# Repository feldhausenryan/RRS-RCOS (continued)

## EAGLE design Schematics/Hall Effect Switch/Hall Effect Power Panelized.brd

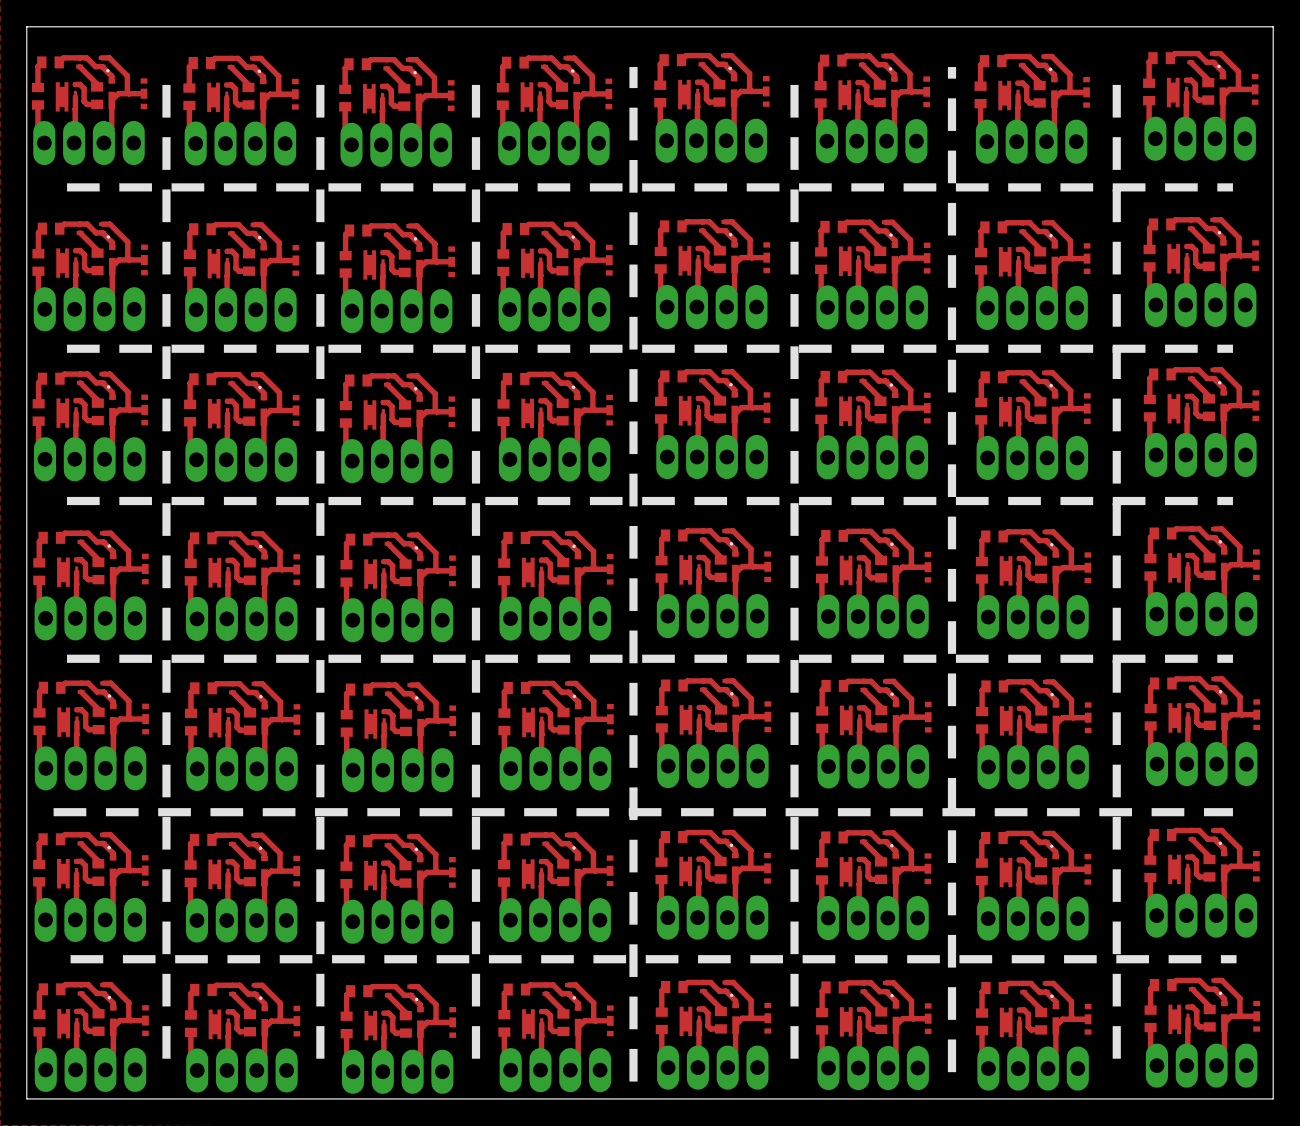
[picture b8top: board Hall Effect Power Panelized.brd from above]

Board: 2 copper layers, 93.0 x 80.0 mm, 560 parts (0 on the bottom side), 337 nets.

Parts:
3.1, 3.2, 3.3, 3.4, 3.5, 3.6, 3.7, 3.8, 3.9, 3.10, 3.11, 3.12, 3.13, 3.14, 3.15, 3.16, 3.17, 3.18, 3.19, 3.20, 3.21, 3.22, 3.23, 3.24, 3.25, 3.26, 3.27, 3.28, 3.29, 3.30, 3.31, 3.32, 3.33, 3.34, 3.35, 3.36, 3.37, 3.38, 3.39, 3.40, 3.41, 3.42, 3.43, 3.44, 3.45, 3.46, 3.47, 3.48, 3.49, 3.50, 3.51, 3.52, 3.53, 3.54, 3.55, 3.56, 3.57, 3.58, 3.59, 3.60, 3.61, 3.62, 3.63, 3.64, 3.65, 3.66, 3.67, 3.68, 3.69, 3.70, 3.71, 3.72, 3.73, 3.74, 3.75, 3.76, 3.77, 3.78, 3.79, 3.80, 3.81, 3.82, 3.83, 3.84, 3.85, 3.86, 3.87, 3.88, 3.89, 3.90, 3.91, 3.92, 3.93, 3.94, 3.95, 3.96, 3.97, 3.98, 3.99, 3.100, 3.101, 3.102, 3.103, 3.104, 3.105, 3.106, 3.107, 3.108, 3.109, 3.110, 3.111, 3.112: RESISTORC0402; C0402
4.7UF, 4.7UF1, 4.7UF2, 4.7UF3, 4.7UF4, 4.7UF5, 4.7UF6, 4.7UF7, 4.7UF8, 4.7UF9, 4.7UF10, 4.7UF11, 4.7UF12, 4.7UF13, 4.7UF14, 4.7UF15, 4.7UF16, 4.7UF17, 4.7UF18, 4.7UF19, 4.7UF20, 4.7UF21, 4.7UF22, 4.7UF23, 4.7UF24, 4.7UF25, 4.7UF26, 4.7UF27, 4.7UF28, 4.7UF29, 4.7UF30, 4.7UF31, 4.7UF32, 4.7UF33, 4.7UF34, 4.7UF35, 4.7UF36, 4.7UF37, 4.7UF38, 4.7UF39, 4.7UF40, 4.7UF41, 4.7UF42, 4.7UF43, 4.7UF44, 4.7UF45, 4.7UF46, 4.7UF47, 4.7UF48, 4.7UF49, 4.7UF50, 4.7UF51, 4.7UF52, 4.7UF53, 4.7UF54, 4.7UF55: CAPACITORC0402; C0402
U$1, U$8, U$15, U$22, U$29, U$36, U$43, U$50, U$57, U$64, U$71, U$78, U$85, U$92, U$99, U$106, U$113, U$120, U$127, U$134, U$141, U$148, U$155, U$162, U$169, U$176, U$183, U$190, U$197, U$204, U$211, U$218, U$225, U$232, U$239, U$246, U$253, U$260, U$267, U$274, U$281, U$288, U$295, U$302, U$309, U$316, U$323, U$330, U$337, U$344, U$351, U$358, U$365, U$372, U$379, U$386: HALL-MOSFET-NEW
U$2, U$9, U$16, U$23, U$30, U$37, U$44, U$51, U$58, U$65, U$72, U$79, U$86, U$93, U$100, U$107, U$114, U$121, U$128, U$135, U$142, U$149, U$156, U$163, U$170, U$177, U$184, U$191, U$198, U$205, U$212, U$219, U$226, U$233, U$240, U$247, U$254, U$261, U$268, U$275, U$282, U$289, U$296, U$303, U$310, U$317, U$324, U$331, U$338, U$345, U$352, U$359, U$366, U$373, U$380, U$387: HALL-HALL-NEW
U$3, U$10, U$17, U$24, U$31, U$38, U$45, U$52, U$59, U$66, U$73, U$80, U$87, U$94, U$101, U$108, U$115, U$122, U$129, U$136, U$143, U$150, U$157, U$164, U$171, U$178, U$185, U$192, U$199, U$206, U$213, U$220, U$227, U$234, U$241, U$248, U$255, U$262, U$269, U$276, U$283, U$290, U$297, U$304, U$311, U$318, U$325, U$332, U$339, U$346, U$353, U$360, U$367, U$374, U$381, U$388: HALL-REG-NEW
U$4, U$5, U$6, U$7, U$11, U$12, U$13, U$14, U$18, U$19, U$20, U$21, U$25, U$26, U$27, U$28, U$32, U$33, U$34, U$35, U$39, U$40, U$41, U$42, U$46, U$47, U$48, U$49, U$53, U$54, U$55, U$56, U$60, U$61, U$62, U$63, U$67, U$68, U$69, U$70, U$74, U$75, U$76, U$77, U$81, U$82, U$83, U$84, U$88, U$89, U$90, U$91, U$95, U$96, U$97, U$98, U$102, U$103, U$104, U$105, U$109, U$110, U$111, U$112, U$116, U$117, U$118, U$119, U$123, U$124, U$125, U$126, U$130, U$131, U$132, U$133, U$137, U$138, U$139, U$140, U$144, U$145, U$146, U$147, U$151, U$152, U$153, U$154, U$158, U$159, U$160, U$161, U$165, U$166, U$167, U$168, U$172, U$173, U$174, U$175, U$179, U$180, U$181, U$182, U$186, U$187, U$188, U$189, U$193, U$194, U$195, U$196, U$200, U$201, U$202, U$203, U$207, U$208, U$209, U$210, U$214, U$215, U$216, U$217, U$221, U$222, U$223, U$224, U$228, U$229, U$230, U$231, U$235, U$236, U$237, U$238, U$242, U$243, U$244, U$245, U$249, U$250, U$251, U$252, U$256, U$257, U$258, U$259, U$263, U$264, U$265, U$266, U$270, U$271, U$272, U$273, U$277, U$278, U$279, U$280, U$284, U$285, U$286, U$287, U$291, U$292, U$293, U$294, U$298, U$299, U$300, U$301, U$305, U$306, U$307, U$308, U$312, U$313, U$314, U$315, U$319, U$320, U$321, U$322, U$326, U$327, U$328, U$329, U$333, U$334, U$335, U$336, U$340, U$341, U$342, U$343, U$347, U$348, U$349, U$350, U$354, U$355, U$356, U$357, U$361, U$362, U$363, U$364, U$368, U$369, U$370, U$371, U$375, U$376, U$377, U$378, U$382, U$383, U$384, U$385, U$389, U$390, U$391, U$392: SINGLE-WIRE

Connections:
GND: 3.3.1, U$2.GND, U$3.2, U$3.5, U$4.P$1, U$7.P$1
GND1: 3.2.1, U$9.GND, U$10.2, U$10.5, U$11.P$1, U$14.P$1
GND2: 3.5.1, U$16.GND, U$17.2, U$17.5, U$18.P$1, U$21.P$1
GND3: 3.7.1, U$23.GND, U$24.2, U$24.5, U$25.P$1, U$28.P$1
GND4: 3.9.1, U$30.GND, U$31.2, U$31.5, U$32.P$1, U$35.P$1
GND5: 3.11.1, U$37.GND, U$38.2, U$38.5, U$39.P$1, U$42.P$1
GND6: 3.13.1, U$44.GND, U$45.2, U$45.5, U$46.P$1, U$49.P$1
GND7: 3.15.1, U$51.GND, U$52.2, U$52.5, U$53.P$1, U$56.P$1
GND8: 3.17.1, U$58.GND, U$59.2, U$59.5, U$60.P$1, U$63.P$1
GND9: 3.19.1, U$65.GND, U$66.2, U$66.5, U$67.P$1, U$70.P$1
GND10: 3.21.1, U$72.GND, U$73.2, U$73.5, U$74.P$1, U$77.P$1
GND11: 3.23.1, U$79.GND, U$80.2, U$80.5, U$81.P$1, U$84.P$1
GND12: 3.25.1, U$86.GND, U$87.2, U$87.5, U$88.P$1, U$91.P$1
GND13: 3.27.1, U$93.GND, U$94.2, U$94.5, U$95.P$1, U$98.P$1
GND14: 3.29.1, U$100.GND, U$101.2, U$101.5, U$102.P$1, U$105.P$1
GND15: 3.31.1, U$107.GND, U$108.2, U$108.5, U$109.P$1, U$112.P$1
GND16: 3.33.1, U$114.GND, U$115.2, U$115.5, U$116.P$1, U$119.P$1
GND17: 3.35.1, U$121.GND, U$122.2, U$122.5, U$123.P$1, U$126.P$1
GND18: 3.37.1, U$128.GND, U$129.2, U$129.5, U$130.P$1, U$133.P$1
GND19: 3.39.1, U$135.GND, U$136.2, U$136.5, U$137.P$1, U$140.P$1
GND20: 3.41.1, U$142.GND, U$143.2, U$143.5, U$144.P$1, U$147.P$1
GND21: 3.43.1, U$149.GND, U$150.2, U$150.5, U$151.P$1, U$154.P$1
GND22: 3.45.1, U$156.GND, U$157.2, U$157.5, U$158.P$1, U$161.P$1
GND23: 3.47.1, U$163.GND, U$164.2, U$164.5, U$165.P$1, U$168.P$1
GND24: 3.49.1, U$170.GND, U$171.2, U$171.5, U$172.P$1, U$175.P$1
GND25: 3.51.1, U$177.GND, U$178.2, U$178.5, U$179.P$1, U$182.P$1
GND26: 3.53.1, U$184.GND, U$185.2, U$185.5, U$186.P$1, U$189.P$1
GND27: 3.55.1, U$191.GND, U$192.2, U$192.5, U$193.P$1, U$196.P$1
GND28: 3.57.1, U$198.GND, U$199.2, U$199.5, U$200.P$1, U$203.P$1
GND29: 3.59.1, U$205.GND, U$206.2, U$206.5, U$207.P$1, U$210.P$1
GND30: 3.61.1, U$212.GND, U$213.2, U$213.5, U$214.P$1, U$217.P$1
GND31: 3.63.1, U$219.GND, U$220.2, U$220.5, U$221.P$1, U$224.P$1
GND32: 3.65.1, U$226.GND, U$227.2, U$227.5, U$228.P$1, U$231.P$1
GND33: 3.67.1, U$233.GND, U$234.2, U$234.5, U$235.P$1, U$238.P$1
GND34: 3.69.1, U$240.GND, U$241.2, U$241.5, U$242.P$1, U$245.P$1
GND35: 3.71.1, U$247.GND, U$248.2, U$248.5, U$249.P$1, U$252.P$1
GND36: 3.73.1, U$254.GND, U$255.2, U$255.5, U$256.P$1, U$259.P$1
GND37: 3.75.1, U$261.GND, U$262.2, U$262.5, U$263.P$1, U$266.P$1
GND38: 3.77.1, U$268.GND, U$269.2, U$269.5, U$270.P$1, U$273.P$1
GND39: 3.79.1, U$275.GND, U$276.2, U$276.5, U$277.P$1, U$280.P$1
GND40: 3.81.1, U$282.GND, U$283.2, U$283.5, U$284.P$1, U$287.P$1
GND41: 3.83.1, U$289.GND, U$290.2, U$290.5, U$291.P$1, U$294.P$1
GND42: 3.85.1, U$296.GND, U$297.2, U$297.5, U$298.P$1, U$301.P$1
GND43: 3.87.1, U$303.GND, U$304.2, U$304.5, U$305.P$1, U$308.P$1
GND44: 3.89.1, U$310.GND, U$311.2, U$311.5, U$312.P$1, U$315.P$1
GND45: 3.91.1, U$317.GND, U$318.2, U$318.5, U$319.P$1, U$322.P$1
GND46: 3.93.1, U$324.GND, U$325.2, U$325.5, U$326.P$1, U$329.P$1
GND47: 3.95.1, U$331.GND, U$332.2, U$332.5, U$333.P$1, U$336.P$1
GND48: 3.97.1, U$338.GND, U$339.2, U$339.5, U$340.P$1, U$343.P$1
GND49: 3.99.1, U$345.GND, U$346.2, U$346.5, U$347.P$1, U$350.P$1
GND50: 3.101.1, U$352.GND, U$353.2, U$353.5, U$354.P$1, U$357.P$1
GND51: 3.103.1, U$359.GND, U$360.2, U$360.5, U$361.P$1, U$364.P$1
GND52: 3.105.1, U$366.GND, U$367.2, U$367.5, U$368.P$1, U$371.P$1
GND53: 3.107.1, U$373.GND, U$374.2, U$374.5, U$375.P$1, U$378.P$1
GND54: 3.109.1, U$380.GND, U$381.2, U$381.5, U$382.P$1, U$385.P$1
GND55: 3.111.1, U$387.GND, U$388.2, U$388.5, U$389.P$1, U$392.P$1
HALL_OUT: 3.1.2, U$2.OUT
HALL_OUT1: 3.4.2, U$9.OUT
HALL_OUT2: 3.6.2, U$16.OUT
HALL_OUT3: 3.8.2, U$23.OUT
HALL_OUT4: 3.10.2, U$30.OUT
HALL_OUT5: 3.12.2, U$37.OUT
HALL_OUT6: 3.14.2, U$44.OUT
HALL_OUT7: 3.16.2, U$51.OUT
HALL_OUT8: 3.18.2, U$58.OUT
HALL_OUT9: 3.20.2, U$65.OUT
HALL_OUT10: 3.22.2, U$72.OUT
HALL_OUT11: 3.24.2, U$79.OUT
HALL_OUT12: 3.26.2, U$86.OUT
HALL_OUT13: 3.28.2, U$93.OUT
HALL_OUT14: 3.30.2, U$100.OUT
HALL_OUT15: 3.32.2, U$107.OUT
HALL_OUT16: 3.34.2, U$114.OUT
HALL_OUT17: 3.36.2, U$121.OUT
HALL_OUT18: 3.38.2, U$128.OUT
HALL_OUT19: 3.40.2, U$135.OUT
HALL_OUT20: 3.42.2, U$142.OUT
HALL_OUT21: 3.44.2, U$149.OUT
HALL_OUT22: 3.46.2, U$156.OUT
HALL_OUT23: 3.48.2, U$163.OUT
HALL_OUT24: 3.50.2, U$170.OUT
HALL_OUT25: 3.52.2, U$177.OUT
HALL_OUT26: 3.54.2, U$184.OUT
HALL_OUT27: 3.56.2, U$191.OUT
HALL_OUT28: 3.58.2, U$198.OUT
HALL_OUT29: 3.60.2, U$205.OUT
HALL_OUT30: 3.62.2, U$212.OUT
HALL_OUT31: 3.64.2, U$219.OUT
HALL_OUT32: 3.66.2, U$226.OUT
HALL_OUT33: 3.68.2, U$233.OUT
HALL_OUT34: 3.70.2, U$240.OUT
HALL_OUT35: 3.72.2, U$247.OUT
HALL_OUT36: 3.74.2, U$254.OUT
HALL_OUT37: 3.76.2, U$261.OUT
HALL_OUT38: 3.78.2, U$268.OUT
HALL_OUT39: 3.80.2, U$275.OUT
HALL_OUT40: 3.82.2, U$282.OUT
HALL_OUT41: 3.84.2, U$289.OUT
HALL_OUT42: 3.86.2, U$296.OUT
HALL_OUT43: 3.88.2, U$303.OUT
HALL_OUT44: 3.90.2, U$310.OUT
HALL_OUT45: 3.92.2, U$317.OUT
HALL_OUT46: 3.94.2, U$324.OUT
HALL_OUT47: 3.96.2, U$331.OUT
HALL_OUT48: 3.98.2, U$338.OUT
HALL_OUT49: 3.100.2, U$345.OUT
HALL_OUT50: 3.102.2, U$352.OUT
HALL_OUT51: 3.104.2, U$359.OUT
HALL_OUT52: 3.106.2, U$366.OUT
HALL_OUT53: 3.108.2, U$373.OUT
HALL_OUT54: 3.110.2, U$380.OUT
HALL_OUT55: 3.112.2, U$387.OUT
unnamed: 4.7UF.2, U$2.CE, U$2.VDD, U$3.4
unnamed: 3.3.2, 4.7UF.1
unnamed: 3.1.1, U$1.G@1
unnamed: 4.7UF1.2, U$9.CE, U$9.VDD, U$10.4
unnamed: 3.2.2, 4.7UF1.1
unnamed: 3.4.1, U$8.G@1
unnamed: 4.7UF2.2, U$16.CE, U$16.VDD, U$17.4
unnamed: 3.5.2, 4.7UF2.1
unnamed: 3.6.1, U$15.G@1
unnamed: 4.7UF3.2, U$23.CE, U$23.VDD, U$24.4
unnamed: 3.7.2, 4.7UF3.1
unnamed: 3.8.1, U$22.G@1
unnamed: 4.7UF4.2, U$30.CE, U$30.VDD, U$31.4
unnamed: 3.9.2, 4.7UF4.1
unnamed: 3.10.1, U$29.G@1
unnamed: 4.7UF5.2, U$37.CE, U$37.VDD, U$38.4
unnamed: 3.11.2, 4.7UF5.1
unnamed: 3.12.1, U$36.G@1
unnamed: 4.7UF6.2, U$44.CE, U$44.VDD, U$45.4
unnamed: 3.13.2, 4.7UF6.1
unnamed: 3.14.1, U$43.G@1
unnamed: 4.7UF7.2, U$51.CE, U$51.VDD, U$52.4
unnamed: 3.15.2, 4.7UF7.1
unnamed: 3.16.1, U$50.G@1
unnamed: 4.7UF8.2, U$58.CE, U$58.VDD, U$59.4
unnamed: 3.17.2, 4.7UF8.1
unnamed: 3.18.1, U$57.G@1
unnamed: 4.7UF9.2, U$65.CE, U$65.VDD, U$66.4
unnamed: 3.19.2, 4.7UF9.1
unnamed: 3.20.1, U$64.G@1
unnamed: 4.7UF10.2, U$72.CE, U$72.VDD, U$73.4
unnamed: 3.21.2, 4.7UF10.1
unnamed: 3.22.1, U$71.G@1
unnamed: 4.7UF11.2, U$79.CE, U$79.VDD, U$80.4
unnamed: 3.23.2, 4.7UF11.1
unnamed: 3.24.1, U$78.G@1
unnamed: 4.7UF12.2, U$86.CE, U$86.VDD, U$87.4
unnamed: 3.25.2, 4.7UF12.1
unnamed: 3.26.1, U$85.G@1
unnamed: 4.7UF13.2, U$93.CE, U$93.VDD, U$94.4
unnamed: 3.27.2, 4.7UF13.1
unnamed: 3.28.1, U$92.G@1
unnamed: 4.7UF14.2, U$100.CE, U$100.VDD, U$101.4
unnamed: 3.29.2, 4.7UF14.1
unnamed: 3.30.1, U$99.G@1
unnamed: 4.7UF15.2, U$107.CE, U$107.VDD, U$108.4
unnamed: 3.31.2, 4.7UF15.1
unnamed: 3.32.1, U$106.G@1
unnamed: 4.7UF16.2, U$114.CE, U$114.VDD, U$115.4
unnamed: 3.33.2, 4.7UF16.1
unnamed: 3.34.1, U$113.G@1
unnamed: 4.7UF17.2, U$121.CE, U$121.VDD, U$122.4
unnamed: 3.35.2, 4.7UF17.1
unnamed: 3.36.1, U$120.G@1
unnamed: 4.7UF18.2, U$128.CE, U$128.VDD, U$129.4
unnamed: 3.37.2, 4.7UF18.1
unnamed: 3.38.1, U$127.G@1
unnamed: 4.7UF19.2, U$135.CE, U$135.VDD, U$136.4
unnamed: 3.39.2, 4.7UF19.1
unnamed: 3.40.1, U$134.G@1
unnamed: 4.7UF20.2, U$142.CE, U$142.VDD, U$143.4
unnamed: 3.41.2, 4.7UF20.1
unnamed: 3.42.1, U$141.G@1
unnamed: 4.7UF21.2, U$149.CE, U$149.VDD, U$150.4
unnamed: 3.43.2, 4.7UF21.1
unnamed: 3.44.1, U$148.G@1
unnamed: 4.7UF22.2, U$156.CE, U$156.VDD, U$157.4
unnamed: 3.45.2, 4.7UF22.1
unnamed: 3.46.1, U$155.G@1
unnamed: 4.7UF23.2, U$163.CE, U$163.VDD, U$164.4
unnamed: 3.47.2, 4.7UF23.1
unnamed: 3.48.1, U$162.G@1
unnamed: 4.7UF24.2, U$170.CE, U$170.VDD, U$171.4
unnamed: 3.49.2, 4.7UF24.1
unnamed: 3.50.1, U$169.G@1
unnamed: 4.7UF25.2, U$177.CE, U$177.VDD, U$178.4
unnamed: 3.51.2, 4.7UF25.1
unnamed: 3.52.1, U$176.G@1
unnamed: 4.7UF26.2, U$184.CE, U$184.VDD, U$185.4
unnamed: 3.53.2, 4.7UF26.1
unnamed: 3.54.1, U$183.G@1
unnamed: 4.7UF27.2, U$191.CE, U$191.VDD, U$192.4
unnamed: 3.55.2, 4.7UF27.1
unnamed: 3.56.1, U$190.G@1
unnamed: 4.7UF28.2, U$198.CE, U$198.VDD, U$199.4
unnamed: 3.57.2, 4.7UF28.1
unnamed: 3.58.1, U$197.G@1
unnamed: 4.7UF29.2, U$205.CE, U$205.VDD, U$206.4
unnamed: 3.59.2, 4.7UF29.1
unnamed: 3.60.1, U$204.G@1
unnamed: 4.7UF30.2, U$212.CE, U$212.VDD, U$213.4
unnamed: 3.61.2, 4.7UF30.1
unnamed: 3.62.1, U$211.G@1
unnamed: 4.7UF31.2, U$219.CE, U$219.VDD, U$220.4
unnamed: 3.63.2, 4.7UF31.1
unnamed: 3.64.1, U$218.G@1
unnamed: 4.7UF32.2, U$226.CE, U$226.VDD, U$227.4
unnamed: 3.65.2, 4.7UF32.1
unnamed: 3.66.1, U$225.G@1
unnamed: 4.7UF33.2, U$233.CE, U$233.VDD, U$234.4
unnamed: 3.67.2, 4.7UF33.1
unnamed: 3.68.1, U$232.G@1
unnamed: 4.7UF34.2, U$240.CE, U$240.VDD, U$241.4
unnamed: 3.69.2, 4.7UF34.1
unnamed: 3.70.1, U$239.G@1
unnamed: 4.7UF35.2, U$247.CE, U$247.VDD, U$248.4
unnamed: 3.71.2, 4.7UF35.1
unnamed: 3.72.1, U$246.G@1
unnamed: 4.7UF36.2, U$254.CE, U$254.VDD, U$255.4
unnamed: 3.73.2, 4.7UF36.1
unnamed: 3.74.1, U$253.G@1
unnamed: 4.7UF37.2, U$261.CE, U$261.VDD, U$262.4
unnamed: 3.75.2, 4.7UF37.1
unnamed: 3.76.1, U$260.G@1
unnamed: 4.7UF38.2, U$268.CE, U$268.VDD, U$269.4
unnamed: 3.77.2, 4.7UF38.1
unnamed: 3.78.1, U$267.G@1
unnamed: 4.7UF39.2, U$275.CE, U$275.VDD, U$276.4
unnamed: 3.79.2, 4.7UF39.1
unnamed: 3.80.1, U$274.G@1
unnamed: 4.7UF40.2, U$282.CE, U$282.VDD, U$283.4
unnamed: 3.81.2, 4.7UF40.1
unnamed: 3.82.1, U$281.G@1
unnamed: 4.7UF41.2, U$289.CE, U$289.VDD, U$290.4
unnamed: 3.83.2, 4.7UF41.1
unnamed: 3.84.1, U$288.G@1
unnamed: 4.7UF42.2, U$296.CE, U$296.VDD, U$297.4
unnamed: 3.85.2, 4.7UF42.1
unnamed: 3.86.1, U$295.G@1
unnamed: 4.7UF43.2, U$303.CE, U$303.VDD, U$304.4
unnamed: 3.87.2, 4.7UF43.1
unnamed: 3.88.1, U$302.G@1
unnamed: 4.7UF44.2, U$310.CE, U$310.VDD, U$311.4
unnamed: 3.89.2, 4.7UF44.1
unnamed: 3.90.1, U$309.G@1
unnamed: 4.7UF45.2, U$317.CE, U$317.VDD, U$318.4
unnamed: 3.91.2, 4.7UF45.1
unnamed: 3.92.1, U$316.G@1
unnamed: 4.7UF46.2, U$324.CE, U$324.VDD, U$325.4
unnamed: 3.93.2, 4.7UF46.1
unnamed: 3.94.1, U$323.G@1
unnamed: 4.7UF47.2, U$331.CE, U$331.VDD, U$332.4
unnamed: 3.95.2, 4.7UF47.1
unnamed: 3.96.1, U$330.G@1
unnamed: 4.7UF48.2, U$338.CE, U$338.VDD, U$339.4
unnamed: 3.97.2, 4.7UF48.1
unnamed: 3.98.1, U$337.G@1
unnamed: 4.7UF49.2, U$345.CE, U$345.VDD, U$346.4
unnamed: 3.99.2, 4.7UF49.1
unnamed: 3.100.1, U$344.G@1
unnamed: 4.7UF50.2, U$352.CE, U$352.VDD, U$353.4
unnamed: 3.101.2, 4.7UF50.1
unnamed: 3.102.1, U$351.G@1
unnamed: 4.7UF51.2, U$359.CE, U$359.VDD, U$360.4
unnamed: 3.103.2, 4.7UF51.1
unnamed: 3.104.1, U$358.G@1
unnamed: 4.7UF52.2, U$366.CE, U$366.VDD, U$367.4
unnamed: 3.105.2, 4.7UF52.1
unnamed: 3.106.1, U$365.G@1
unnamed: 4.7UF53.2, U$373.CE, U$373.VDD, U$374.4
unnamed: 3.107.2, 4.7UF53.1
unnamed: 3.108.1, U$372.G@1
unnamed: 4.7UF54.2, U$380.CE, U$380.VDD, U$381.4
unnamed: 3.109.2, 4.7UF54.1
unnamed: 3.110.1, U$379.G@1
unnamed: 4.7UF55.2, U$387.CE, U$387.VDD, U$388.4
unnamed: 3.111.2, 4.7UF55.1
unnamed: 3.112.1, U$386.G@1
VIN: U$1.D#4, U$1.D@1, U$1.D@2, U$1.D@3, U$1.D@5, U$3.1, U$3.3, U$6.P$1, U$8.D#4, U$8.D@1, U$8.D@2, U$8.D@3, U$8.D@5, U$10.1, U$10.3, U$13.P$1, U$15.D#4, U$15.D@1, U$15.D@2, U$15.D@3, U$15.D@5, U$17.1, U$17.3, U$20.P$1, U$22.D#4, U$22.D@1, U$22.D@2, U$22.D@3, U$22.D@5, U$24.1, U$24.3, U$27.P$1, U$29.D#4, U$29.D@1, U$29.D@2, U$29.D@3, U$29.D@5, U$31.1, U$31.3, U$34.P$1, U$36.D#4, U$36.D@1, U$36.D@2, U$36.D@3, U$36.D@5, U$38.1, U$38.3, U$41.P$1, U$43.D#4, U$43.D@1, U$43.D@2, U$43.D@3, U$43.D@5, U$45.1, U$45.3, U$48.P$1, U$50.D#4, U$50.D@1, U$50.D@2, U$50.D@3, U$50.D@5, U$52.1, U$52.3, U$55.P$1, U$57.D#4, U$57.D@1, U$57.D@2, U$57.D@3, U$57.D@5, U$59.1, U$59.3, U$62.P$1, U$64.D#4, U$64.D@1, U$64.D@2, U$64.D@3, U$64.D@5, U$66.1, U$66.3, U$69.P$1, U$71.D#4, U$71.D@1, U$71.D@2, U$71.D@3, U$71.D@5, U$73.1, U$73.3, U$76.P$1, U$78.D#4, U$78.D@1, U$78.D@2, U$78.D@3, U$78.D@5, U$80.1, U$80.3, U$83.P$1, U$85.D#4, U$85.D@1, U$85.D@2, U$85.D@3, U$85.D@5, U$87.1, U$87.3, U$90.P$1, U$92.D#4, U$92.D@1, U$92.D@2, U$92.D@3, U$92.D@5, U$94.1, U$94.3, U$97.P$1, U$99.D#4, U$99.D@1, U$99.D@2, U$99.D@3, U$99.D@5, U$101.1, U$101.3, U$104.P$1, U$106.D#4, U$106.D@1, U$106.D@2, U$106.D@3, U$106.D@5, U$108.1, U$108.3, U$111.P$1, U$113.D#4, U$113.D@1, U$113.D@2, U$113.D@3, U$113.D@5, U$115.1, U$115.3, U$118.P$1, U$120.D#4, U$120.D@1, U$120.D@2, U$120.D@3, U$120.D@5, U$122.1, U$122.3, U$125.P$1, U$127.D#4, U$127.D@1, U$127.D@2, U$127.D@3, U$127.D@5, U$129.1, U$129.3, U$132.P$1, U$134.D#4, U$134.D@1, U$134.D@2, U$134.D@3, U$134.D@5, U$136.1, U$136.3, U$139.P$1, U$141.D#4, U$141.D@1, U$141.D@2, U$141.D@3, U$141.D@5, U$143.1, U$143.3, U$146.P$1, U$148.D#4, U$148.D@1, U$148.D@2, U$148.D@3, U$148.D@5, U$150.1, U$150.3, U$153.P$1, U$155.D#4, U$155.D@1, U$155.D@2, U$155.D@3, U$155.D@5, U$157.1, U$157.3, U$160.P$1, U$162.D#4, U$162.D@1, U$162.D@2, U$162.D@3, U$162.D@5, U$164.1, U$164.3, U$167.P$1, U$169.D#4, U$169.D@1, U$169.D@2, U$169.D@3, U$169.D@5, U$171.1, U$171.3, U$174.P$1, U$176.D#4, U$176.D@1, U$176.D@2, U$176.D@3, U$176.D@5, U$178.1, U$178.3, U$181.P$1, U$183.D#4, U$183.D@1, U$183.D@2, U$183.D@3, U$183.D@5, U$185.1, U$185.3, U$188.P$1, U$190.D#4, U$190.D@1, U$190.D@2, U$190.D@3, U$190.D@5, U$192.1, U$192.3, U$195.P$1, U$197.D#4, U$197.D@1, U$197.D@2, U$197.D@3, U$197.D@5, U$199.1, U$199.3, U$202.P$1, U$204.D#4, U$204.D@1, U$204.D@2, U$204.D@3, U$204.D@5, U$206.1, U$206.3, U$209.P$1, U$211.D#4, U$211.D@1, U$211.D@2, U$211.D@3, U$211.D@5, U$213.1, U$213.3, U$216.P$1, U$218.D#4, U$218.D@1, U$218.D@2, U$218.D@3, U$218.D@5, U$220.1, U$220.3, U$223.P$1, U$225.D#4, U$225.D@1, U$225.D@2, U$225.D@3, U$225.D@5, U$227.1, U$227.3, U$230.P$1, U$232.D#4, U$232.D@1, U$232.D@2, U$232.D@3, U$232.D@5, U$234.1, U$234.3, U$237.P$1, U$239.D#4, U$239.D@1, U$239.D@2, U$239.D@3, U$239.D@5, U$241.1, U$241.3, U$244.P$1, U$246.D#4, U$246.D@1, U$246.D@2, U$246.D@3, U$246.D@5, U$248.1, U$248.3, U$251.P$1, U$253.D#4, U$253.D@1, U$253.D@2, U$253.D@3, U$253.D@5, U$255.1, U$255.3, U$258.P$1, U$260.D#4, U$260.D@1, U$260.D@2, U$260.D@3, U$260.D@5, U$262.1, U$262.3, U$265.P$1, U$267.D#4, U$267.D@1, U$267.D@2, U$267.D@3, U$267.D@5, U$269.1, U$269.3, U$272.P$1, U$274.D#4, U$274.D@1, U$274.D@2, U$274.D@3, U$274.D@5, U$276.1, U$276.3, U$279.P$1, U$281.D#4, U$281.D@1, U$281.D@2, U$281.D@3, U$281.D@5, U$283.1, U$283.3, U$286.P$1, U$288.D#4, U$288.D@1, U$288.D@2, U$288.D@3, U$288.D@5, U$290.1, U$290.3, U$293.P$1, U$295.D#4, U$295.D@1, U$295.D@2, U$295.D@3, U$295.D@5, U$297.1, U$297.3, U$300.P$1, U$302.D#4, U$302.D@1, U$302.D@2, U$302.D@3, U$302.D@5, U$304.1, U$304.3, U$307.P$1, U$309.D#4, U$309.D@1, U$309.D@2, U$309.D@3, U$309.D@5, U$311.1, U$311.3, U$314.P$1, U$316.D#4, U$316.D@1, U$316.D@2, U$316.D@3, U$316.D@5, U$318.1, U$318.3, U$321.P$1, U$323.D#4, U$323.D@1, U$323.D@2, U$323.D@3, U$323.D@5, U$325.1, U$325.3, U$328.P$1, U$330.D#4, U$330.D@1, U$330.D@2, U$330.D@3, U$330.D@5, U$332.1, U$332.3, U$335.P$1, U$337.D#4, U$337.D@1, U$337.D@2, U$337.D@3, U$337.D@5, U$339.1, U$339.3, U$342.P$1, U$344.D#4, U$344.D@1, U$344.D@2, U$344.D@3, U$344.D@5, U$346.1, U$346.3, U$349.P$1, U$351.D#4, U$351.D@1, U$351.D@2, U$351.D@3, U$351.D@5, U$353.1, U$353.3, U$356.P$1, U$358.D#4, U$358.D@1, U$358.D@2, U$358.D@3, U$358.D@5, U$360.1, U$360.3, U$363.P$1, U$365.D#4, U$365.D@1, U$365.D@2, U$365.D@3, U$365.D@5, U$367.1, U$367.3, U$370.P$1, U$372.D#4, U$372.D@1, U$372.D@2, U$372.D@3, U$372.D@5, U$374.1, U$374.3, U$377.P$1, U$379.D#4, U$379.D@1, U$379.D@2, U$379.D@3, U$379.D@5, U$381.1, U$381.3, U$384.P$1, U$386.D#4, U$386.D@1, U$386.D@2, U$386.D@3, U$386.D@5, U$388.1, U$388.3, U$391.P$1
VIN_OUT: U$1.S@1, U$1.S@2, U$5.P$1
VIN_OUT1: U$8.S@1, U$8.S@2, U$12.P$1
VIN_OUT2: U$15.S@1, U$15.S@2, U$19.P$1
VIN_OUT3: U$22.S@1, U$22.S@2, U$26.P$1
VIN_OUT4: U$29.S@1, U$29.S@2, U$33.P$1
VIN_OUT5: U$36.S@1, U$36.S@2, U$40.P$1
VIN_OUT6: U$43.S@1, U$43.S@2, U$47.P$1
VIN_OUT7: U$50.S@1, U$50.S@2, U$54.P$1
VIN_OUT8: U$57.S@1, U$57.S@2, U$61.P$1
VIN_OUT9: U$64.S@1, U$64.S@2, U$68.P$1
VIN_OUT10: U$71.S@1, U$71.S@2, U$75.P$1
VIN_OUT11: U$78.S@1, U$78.S@2, U$82.P$1
VIN_OUT12: U$85.S@1, U$85.S@2, U$89.P$1
VIN_OUT13: U$92.S@1, U$92.S@2, U$96.P$1
VIN_OUT14: U$99.S@1, U$99.S@2, U$103.P$1
VIN_OUT15: U$106.S@1, U$106.S@2, U$110.P$1
VIN_OUT16: U$113.S@1, U$113.S@2, U$117.P$1
VIN_OUT17: U$120.S@1, U$120.S@2, U$124.P$1
VIN_OUT18: U$127.S@1, U$127.S@2, U$131.P$1
VIN_OUT19: U$134.S@1, U$134.S@2, U$138.P$1
VIN_OUT20: U$141.S@1, U$141.S@2, U$145.P$1
VIN_OUT21: U$148.S@1, U$148.S@2, U$152.P$1
VIN_OUT22: U$155.S@1, U$155.S@2, U$159.P$1
VIN_OUT23: U$162.S@1, U$162.S@2, U$166.P$1
VIN_OUT24: U$169.S@1, U$169.S@2, U$173.P$1
VIN_OUT25: U$176.S@1, U$176.S@2, U$180.P$1
VIN_OUT26: U$183.S@1, U$183.S@2, U$187.P$1
VIN_OUT27: U$190.S@1, U$190.S@2, U$194.P$1
VIN_OUT28: U$197.S@1, U$197.S@2, U$201.P$1
VIN_OUT29: U$204.S@1, U$204.S@2, U$208.P$1
VIN_OUT30: U$211.S@1, U$211.S@2, U$215.P$1
VIN_OUT31: U$218.S@1, U$218.S@2, U$222.P$1
VIN_OUT32: U$225.S@1, U$225.S@2, U$229.P$1
VIN_OUT33: U$232.S@1, U$232.S@2, U$236.P$1
VIN_OUT34: U$239.S@1, U$239.S@2, U$243.P$1
VIN_OUT35: U$246.S@1, U$246.S@2, U$250.P$1
VIN_OUT36: U$253.S@1, U$253.S@2, U$257.P$1
VIN_OUT37: U$260.S@1, U$260.S@2, U$264.P$1
VIN_OUT38: U$267.S@1, U$267.S@2, U$271.P$1
VIN_OUT39: U$274.S@1, U$274.S@2, U$278.P$1
VIN_OUT40: U$281.S@1, U$281.S@2, U$285.P$1
VIN_OUT41: U$288.S@1, U$288.S@2, U$292.P$1
VIN_OUT42: U$295.S@1, U$295.S@2, U$299.P$1
VIN_OUT43: U$302.S@1, U$302.S@2, U$306.P$1
VIN_OUT44: U$309.S@1, U$309.S@2, U$313.P$1
VIN_OUT45: U$316.S@1, U$316.S@2, U$320.P$1
VIN_OUT46: U$323.S@1, U$323.S@2, U$327.P$1
VIN_OUT47: U$330.S@1, U$330.S@2, U$334.P$1
VIN_OUT48: U$337.S@1, U$337.S@2, U$341.P$1
VIN_OUT49: U$344.S@1, U$344.S@2, U$348.P$1
VIN_OUT50: U$351.S@1, U$351.S@2, U$355.P$1
VIN_OUT51: U$358.S@1, U$358.S@2, U$362.P$1
VIN_OUT52: U$365.S@1, U$365.S@2, U$369.P$1
VIN_OUT53: U$372.S@1, U$372.S@2, U$376.P$1
VIN_OUT54: U$379.S@1, U$379.S@2, U$383.P$1
VIN_OUT55: U$386.S@1, U$386.S@2, U$390.P$1

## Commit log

2016-08-23 Included Old Work
    Hall Effect Switch
    Drag Flap Boards
2016-09-01 Huge chunk of schematic work
    Fixed errors in hall effect board
    Major work done to the control board schematic
    Library made for the control board schematic
2016-09-02 Rocket Control Board Work
    Significant changes to rocket control board. Too many to detail.
2016-09-07 Added Regulator Part
    See Title
2016-09-07 Closed -> Open Source Changes
    Modified readme text
2016-09-13 Added picture of board
    Added a screenshot of the board in eagle.
2016-09-13 Added regulator and supporting components
2016-09-20 misc changes
2016-09-20 updated hall effect switch
2016-09-20 Fixed Hall Effect Switch Again
    (Lets hope!)
2016-09-20 Added Diode, Began Routing
2016-09-20 Misc
2016-09-20 Misc Routing
2016-10-14 Ver 4
2016-10-14 Board Ordered!
2016-11-08 Weeks Worth of Stuff
    Cleaned up folder system
    New boards
    New library parts
    Updated Readmes
    Added blog posts.
2016-12-14 Final commit for the semester
    Various board changes.
2017-01-27 Rocket Club Library additions
    Added a couple of libraries that will be used for rocket club.
    Added the MKRZero board to the respoitory for reference.
2017-02-03 Version 6
    Version 6 of the board
    Next blog post
    Added ULP Scripts that help make a bill of materials.
2017-02-04 Another blog post + next order
    Pics for the next blod post
    Gerber files for the next PCB order. PLUS STENCIL
2017-04-13 Tons of Changes
    Too many to describe. Most of the semester board design and rocket club
    stuff.
2017-04-19 New Crystal and Regualtor
    Title
2017-04-19 Bod Post Stuff
2017-04-20 New Hall Effect Switch
    Changed all the parts for the hall effect switch.
    The goal is lower passive power consumption and lower Rds(on).
    Panelized the new hall effect switch.
